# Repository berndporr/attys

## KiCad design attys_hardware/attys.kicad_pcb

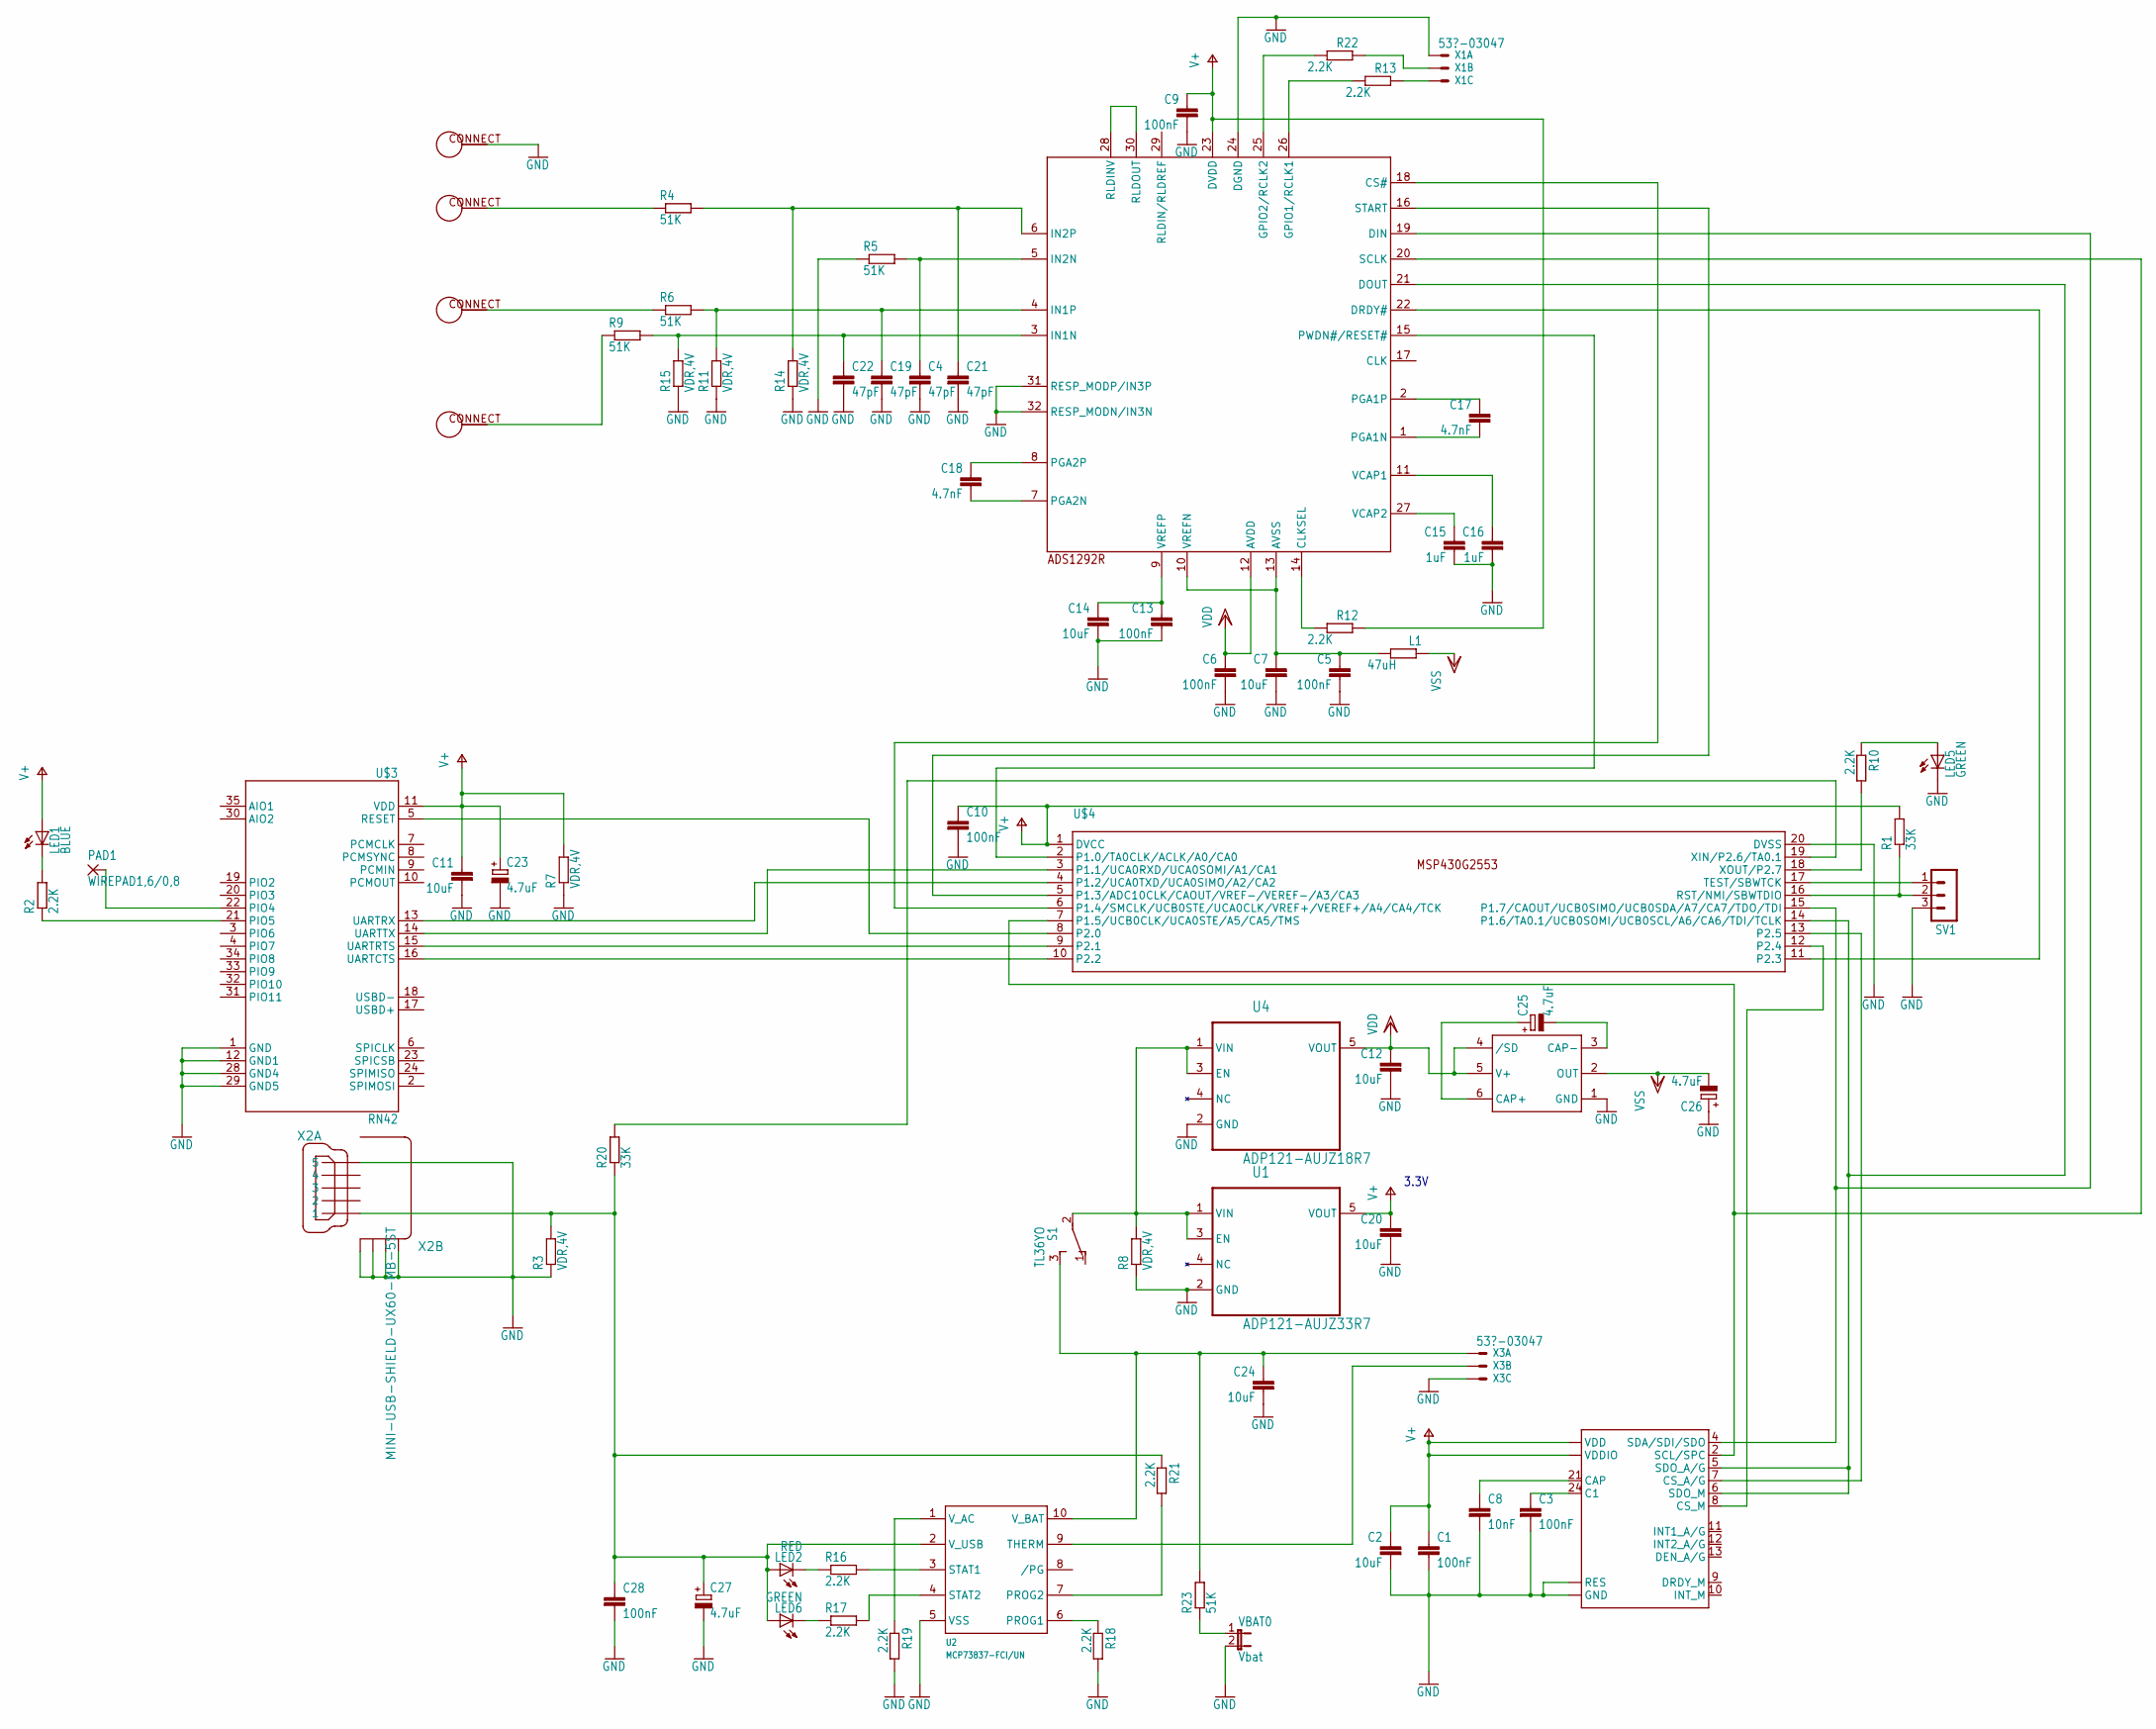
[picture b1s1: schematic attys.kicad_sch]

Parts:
ADS1292R0: ADS1292R; TQFP-32
C1, C3, C5, C6, C9, C10, C13, C28: 100nF; C0603
C2, C7, C11, C12, C14, C20, C24: 10uF; C1206
C4, C19, C21, C22: 47pF; C0603
C8: 10nF; C0603
C15, C16: 1uF; C0603
C17, C18: 4.7nF; C0603
C23, C25, C26, C27: 4.7uF; SMC_C
L1: 47uH; R0805
LED1: BLUE; CHIPLED_0805
LED2: RED; CHIPLED_0805
LED5, LED6: GREEN; CHIPLED_0805
PAD1: WIREPAD1,6/0,8; 1,6_0,8
R1, R20: 33K; R0603
R2, R10, R12, R13, R16, R17, R18, R19, R21, R22: 2.2K; R0603
R3, R7, R8, R11, R14, R15: VDR,4V; R0805
R4, R5, R6, R9, R23: 51K; R0603
S1: TL36YO; TL3XYO
SV1: MA03-1
U1: ADP121-AUJZ33R7; SOT95P280X100-5N; MPN ADP121-AUJZ33R7
U2: MCP73837-FCI/UN; MSOP10
U4: ADP121-AUJZ18R7; SOT95P280X100-5N; MPN ADP121-AUJZ33R7
U5: LSM9DS1; LGA24-8X4
U$3: RN42; SPARKFUN_RN41
U$4: MSP430G2553; TSSOP20
U$5, U$7, U$9, U$10: 4MMCONNECT
U$12: LM2664; SOT-23-5
VBAT0: Vbat; JP1
X1, X3: 53?-03047; 53047-03; MPN 530470310
X2: MINI-USB-SHIELD-UX60-MB-5ST; UX60-MB-5ST

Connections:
+5V: C27.+, C28.1, LED2.A, LED6.A, R3.2, R20.1, R21.1, U2.2 (V_USB), X2.1
CS/: U5.8 (CS_M), U$4.12 (P2.4)
ECG_/CS: ADS1292R0.18 (CS#), U$4.6 (P1.4/SMCLK/UCB0STE/UCA0CLK/VREF+/VEREF+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)
ECG_/DRDY: ADS1292R0.22 (DRDY#), U$4.11 (P2.3)
ECG_START: ADS1292R0.16 (START), U$4.5 (P1.3/ADC10CLK/CAOUT/VREF-/VEREF-/A3/CA3)
GND: ADS1292R0.24 (DGND), ADS1292R0.31 (RESP_MODP/IN3P), ADS1292R0.32 (RESP_MODN/IN3N), C1.2, C2.2, C3.2, C4.2, C5.2, C6.2, C7.2, C8.2, C9.2, C10.2, C11.2, C12.2, C13.2, C14.2, C15.2, C16.2, C19.2, C20.2, C21.2, C22.2, C23.-, C24.2, C26.+, C27.-, C28.2, LED5.C, R3.1, R5.1, R7.1, R8.1, R11.1, R14.1, R15.1, R18.2, R19.2, SV1.3, U1.2 (GND), U2.5 (VSS), U4.2 (GND), U5.14 (RES), U5.15 (RES), U5.16 (RES), U5.17 (RES), U5.18 (RES), U5.19 (GND), U5.20 (GND), U$3.1 (GND), U$3.12 (GND1), U$3.28 (GND4), U$3.29 (GND5), U$4.20 (DVSS), U$5.CONNECT, U$12.1 (GND), VBAT0.2, X1.1, X2.5, X2.M1 (S1), X2.M2 (S2), X2.M3 (S3), X2.M4 (S4), X3.3
unnamed: R1.1, SV1.2, U$4.16 (RST/NMI/SBWTDIO)
unnamed: U$3.13 (UARTRX), U$4.4 (P1.2/UCA0TXD/UCA0SIMO/A2/CA2)
unnamed: ADS1292R0.28 (RLDINV), ADS1292R0.30 (RLDOUT)
unnamed: ADS1292R0.5 (IN2N), C4.1, R5.2
unnamed: SV1.1, U$4.17 (TEST/SBWTCK)
unnamed: U$3.14 (UARTTX), U$4.3 (P1.1/UCA0RXD/UCA0SOMI/A1/CA1)
unnamed: U$3.15 (UARTRTS), U$4.9 (P2.1)
unnamed: U$3.16 (UARTCTS), U$4.10 (P2.2)
unnamed: U$3.5 (RESET), U$4.8 (P2.0)
unnamed: R2.1, U$3.21 (PIO5)
unnamed: R8.2, S1.2, U1.1 (VIN), U1.3 (EN), U4.1 (VIN), U4.3 (EN)
unnamed: ADS1292R0.10 (VREFN), ADS1292R0.13 (AVSS), C5.1, C7.1, L1.2
unnamed: PAD1.1, U$3.22 (PIO4)
unnamed: R10.2, U$4.18 (XOUT/P2.7)
unnamed: LED5.A, R10.1
unnamed: LED1.C, R2.2
unnamed: ADS1292R0.25 (GPIO2/RCLK2), R22.2
unnamed: ADS1292R0.9 (VREFP), C13.1, C14.1
unnamed: ADS1292R0.27 (VCAP2), C15.1
unnamed: ADS1292R0.26 (GPIO1/RCLK1), R13.2
unnamed: ADS1292R0.11 (VCAP1), C16.1
unnamed: R20.2, U$4.19 (XIN/P2.6/TA0.1)
unnamed: ADS1292R0.15 (PWDN#/RESET#), U$4.2 (P1.0/TA0CLK/ACLK/A0/CA0)
unnamed: U5.7 (CS_A/G), U$4.13 (P2.5)
unnamed: C3.1, U5.24 (C1)
unnamed: C8.1, U5.21 (CAP)
unnamed: R13.1, X1.3
unnamed: R22.1, X1.2
unnamed: R23.1, VBAT0.1
unnamed: ADS1292R0.2 (PGA1P), C17.1
unnamed: ADS1292R0.1 (PGA1N), C17.2
unnamed: ADS1292R0.8 (PGA2P), C18.1
unnamed: ADS1292R0.7 (PGA2N), C18.2
unnamed: ADS1292R0.14 (CLKSEL), R12.2
unnamed: ADS1292R0.6 (IN2P), C21.1, R4.2, R14.2
unnamed: ADS1292R0.3 (IN1N), C22.1, R9.2, R15.2
unnamed: ADS1292R0.4 (IN1P), C19.1, R6.2, R11.2
unnamed: R4.1, U$7.CONNECT
unnamed: R9.1, U$10.CONNECT
unnamed: R6.1, U$9.CONNECT
unnamed: C24.1, R23.2, S1.3 (S), U2.10 (V_BAT), X3.1
unnamed: C25.+, U$12.6 (CAP+)
unnamed: C25.-, U$12.3 (CAP-)
unnamed: R16.2, U2.3 (STAT1)
unnamed: LED6.C, R17.1
unnamed: R17.2, U2.4 (STAT2)
unnamed: LED2.C, R16.1
unnamed: R18.1, U2.6 (PROG1)
unnamed: U2.9 (THERM), X3.2
unnamed: R19.1, U2.1 (V_AC)
unnamed: R21.2, U2.7 (PROG2)
SPI_CLK: ADS1292R0.20 (SCLK), U5.2 (SCL/SPC), U$4.7 (P1.5/UCB0CLK/UCA0STE/A5/CA5/TMS)
SPI_MISO: ADS1292R0.21 (DOUT), U5.5 (SDO_A/G), U5.6 (SDO_M), U$4.14 (P1.6/TA0.1/UCB0SOMI/UCB0SCL/A6/CA6/TDI/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)
SPI_MOSI: ADS1292R0.19 (DIN), U5.4 (SDA/SDI/SDO), U$4.15 (P1.7/CAOUT/UCB0SIMO/UCB0SDA/A7/CA7/TDO/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)
V+: ADS1292R0.23 (DVDD), C1.1, C2.1, C9.1, C10.1, C11.1, C20.1, C23.+, LED1.A, R1.2, R7.2, R12.1, U1.5 (VOUT), U5.1 (VDDIO), U5.3 (VDDIO), U5.22 (VDD), U5.23 (VDD), U$3.11 (VDD), U$4.1 (DVCC)
VDD: ADS1292R0.12 (AVDD), C6.1, C12.1, U4.5 (VOUT), U$12.4 (/SD), U$12.5 (V+)
VSS: C26.-, L1.1, U$12.2 (OUT)

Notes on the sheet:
3.3V

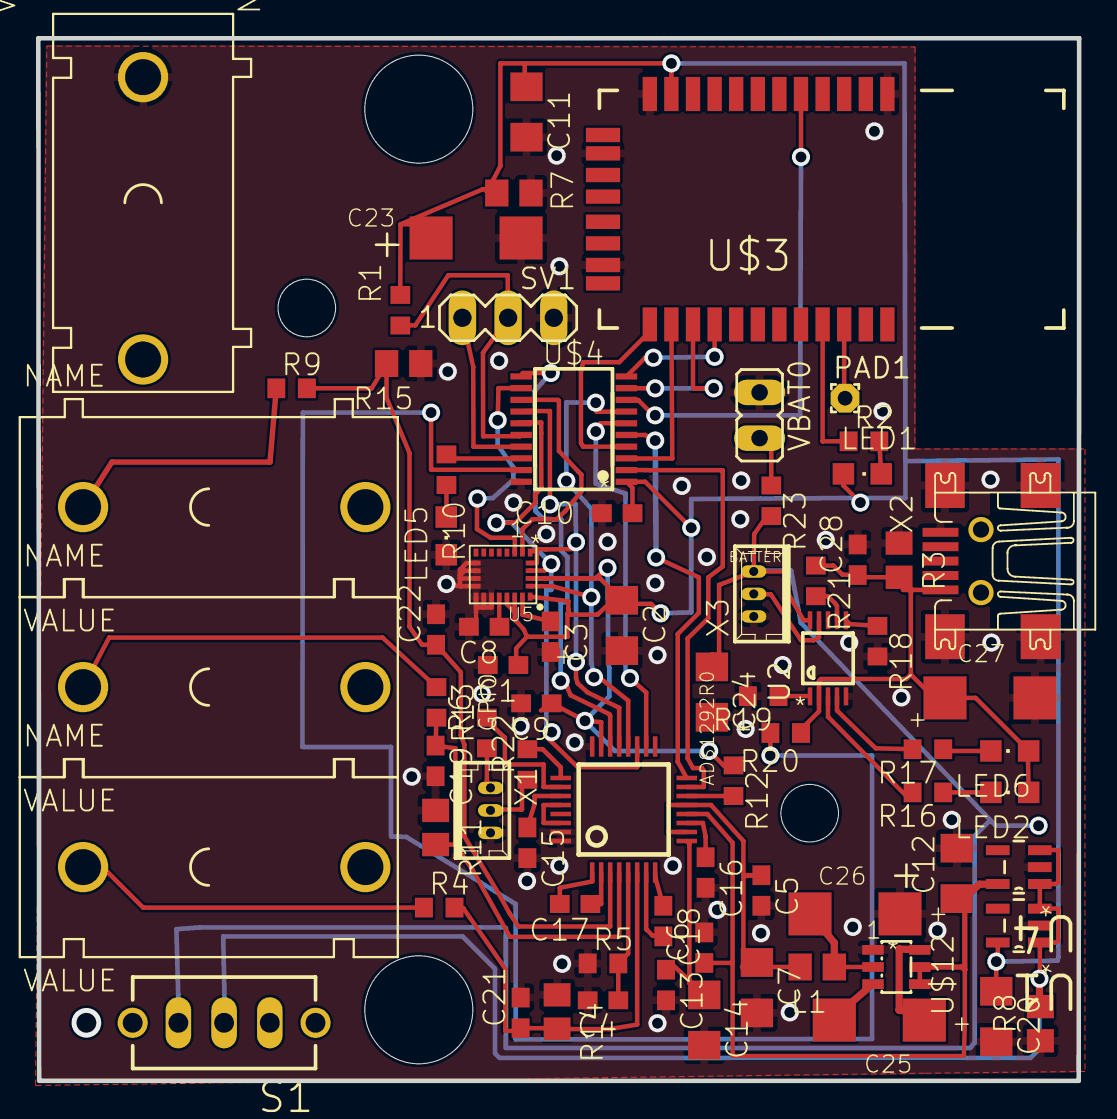
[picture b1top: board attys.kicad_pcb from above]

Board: 2 copper layers, 57.8 x 57.9 mm, 79 parts (0 on the bottom side), 63 nets.

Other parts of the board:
UNK_HOLE_0: dummyfp0
UNK_HOLE_1: dummyfp1
UNK_HOLE_2: dummyfp2
UNK_HOLE_3: dummyfp3
